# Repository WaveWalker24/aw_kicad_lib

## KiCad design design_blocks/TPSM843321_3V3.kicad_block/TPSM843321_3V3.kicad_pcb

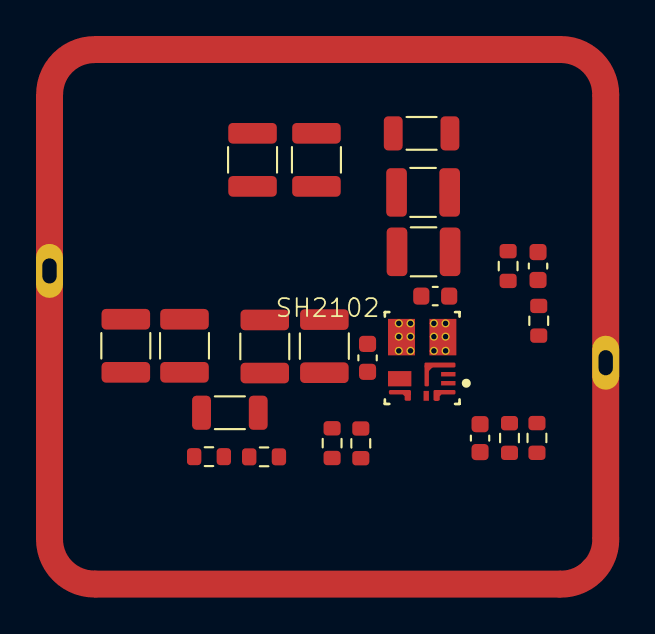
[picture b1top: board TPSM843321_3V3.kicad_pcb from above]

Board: 6 copper layers, 25 parts (0 on the bottom side), 10 nets, no tracks yet.

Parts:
C2017, C2018, C2019, C2020, C2038, C2039, C2040, C2041: 22uF; C_1210_3225Metric
C2021: 33nF; C_0603_1608Metric
C2022, C2024: 100nF; C_0603_1608Metric
C2023: 22pF; C_0603_1608Metric
FB2003, FB2004: 220Ohm @ 100MHz; L_1206_3216Metric
R2026, R2028, R2029: 0R; R_0603_1608Metric
R2030: 46.4k; R_0603_1608Metric
R2034: 10k; R_0603_1608Metric
R2035, R2036, R2037: 100k; R_0603_1608Metric
SH2102: RFShield_TwoPieces_Frame_W31.2mm_L30mm_H5mm; MS312-10
SH2103: RFShield_TwoPieces_Cover_W31.2mm_L30mm_H5mm; MS312-10C
U2003: TPSM843321RCJR; RCJ0009A-MFG

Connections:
/VDD_12V: C2017.1, C2018.1, FB2003.1, R2035.1
/fpga/PG: C2021.1, R2037.2, U2003.8 (SS_PG)
/fpga/TPS_VIN: C2019.1, C2020.1, C2022.1, FB2003.2, R2037.1, U2003.6 (VIN)
/fpga/TPS_VOUT: C2023.1, C2024.1, C2038.1, C2039.1, FB2004.1, R2030.1, U2003.4 (VOUT)
/fpga/VDD_3V3: C2040.1, C2041.1, FB2004.2
GND: C2017.2, C2018.2, C2019.2, C2020.2, C2021.2, C2022.2, C2024.2, C2038.2, C2039.2, C2040.2, C2041.2, R2028.2, R2029.2, R2034.2, R2036.2, SH2102.1 (Shield_1), U2003.3 (GND)
unnamed: R2026.2, R2035.2, R2036.1, U2003.1 (EN)
unnamed: C2023.2, R2030.2, R2034.1, U2003.2 (FB)
unnamed: R2029.1, U2003.7 (MODE)
unnamed: R2028.1, U2003.9 (RT_SYNC)

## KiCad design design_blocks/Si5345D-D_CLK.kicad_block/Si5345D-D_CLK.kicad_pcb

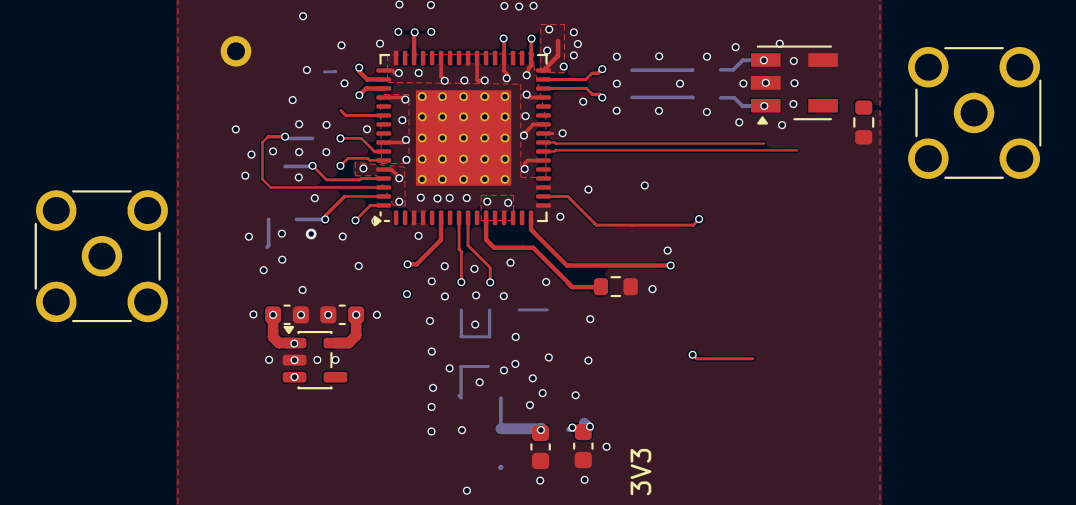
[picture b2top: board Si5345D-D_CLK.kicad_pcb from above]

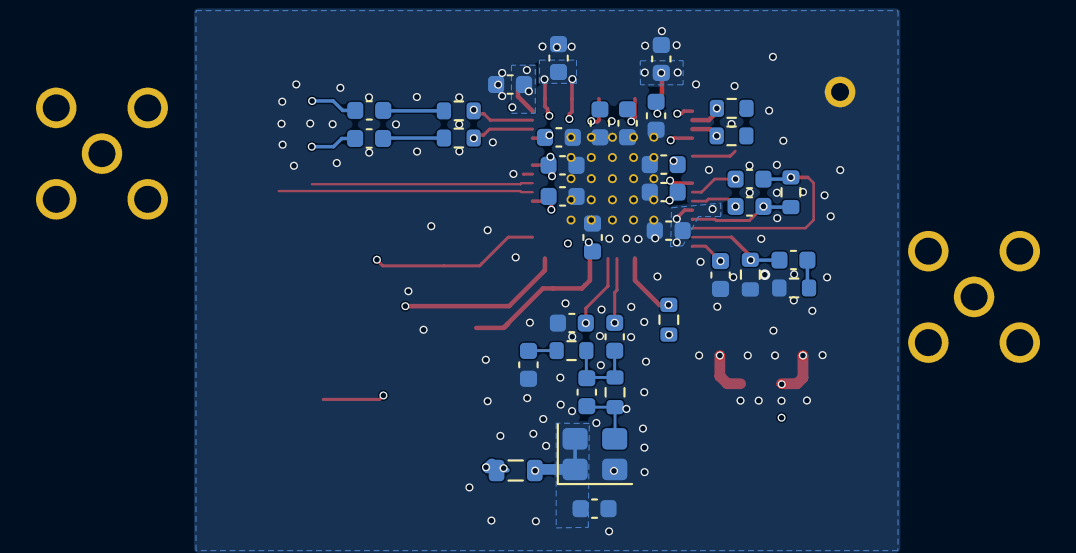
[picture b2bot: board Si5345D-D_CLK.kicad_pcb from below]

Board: 8 copper layers, 48 parts (36 on the bottom side), 28 nets.

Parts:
C6: 12pF; C_0603_1608Metric
C7, C8, C9, C15, C16, C17, C27, C30, C31, C1053: 100nF; C_0603_1608Metric
C10, C11, C1009, C1024, C1042, C1043, C1044, C1045, C1046, C1047, C1048, C1049, C1050, C1051, C1052, C1072, C1073: 1uF; C_0603_1608Metric
D2001, D2002: ESD_3.3V; R_0603_1608Metric
FB1003: 600 Ohm @ 100 MHz; L_0805_2012Metric
J1, J2: Conn_Coaxial_Small; SMA_Molex_73251-2200_Horizontal
J4011: TP; Testpoint_2.54mm
R24: 453R; R_0603_1608Metric
R25: 549R; R_0603_1608Metric
R30: 10k; R_0603_1608Metric
R31: 100R; R_0603_1608Metric
R37: 49.9R; R_0603_1608Metric
R1033, R1034, R4001, R4010: 28; R_0603_1608Metric
R1057: 4.75k; R_0603_1608Metric
TR4001: TC2-1TX+; Mini-Circuits_AT1521
U4: Si5345D-D; QFN-64-1EP_9x9mm_P0.5mm_EP5.3x5.3mm_ThermalVias
U1023: ADP150AUJZ-1.8-R7; TSOT-23-5
Y1: 7X48070007

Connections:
/3V3: C1042.1, C1043.1, C1044.1, C1045.1, C1046.1, C1047.1, C1048.1, C1049.1, C1051.1, C1052.1, C1072.1, R1057.1, U4.13 (VDDA), U4.22 (VDDO0), U4.26 (VDDO1), U4.29 (VDDO2), U4.33 (VDDO3), U4.36 (VDDO4), U4.39 (I2C_SEL), U4.40 (VDDO5), U4.43 (VDDO6), U4.49 (VDDO7), U4.52 (VDDO8), U4.57 (VDDO9), U1023.1 (VIN), U1023.3 (EN)
/clk/1V8: C1009.1, C1024.1, C1050.1, C1073.1, J4011.1 (Pin_1_1), U4.32 (VDD), U4.46 (VDD), U4.60 (VDD), U1023.5 (VOUT)
/clk/3.3V: C10.1, FB1003.1
/clk/3V3_XO: C11.1, C1053.1, FB1003.2, Y1.1 (EN), Y1.4 (Vdd)
/clk/CLK_OUT_N: C27.1, R1033.2
/clk/CLK_OUT_P: C17.1, R1034.2
/clk/Clock Out: D2002.1 (A1), J2.1 (In), TR4001.6 (Primary_Dot)
/clk/RESET: R1057.2, U4.6 (~RST)
/clk/XA: C8.1, U4.8 (XA)
/clk/XB: C9.2, U4.9 (XB)
/clk/Zero_Delay_N: C16.2, U4.58 (OUT9b)
/clk/Zero_Delay_P: C15.2, U4.59 (OUT9)
GND: C7.1, C9.1, C10.2, C11.2, C31.1, C1009.2, C1024.2, C1042.2, C1043.2, C1044.2, C1045.2, C1046.2, C1047.2, C1048.2, C1049.2, C1050.2, C1051.2, C1052.2, C1053.2, C1072.2, C1073.2, D2001.2 (A2), D2002.2 (A2), J1.2 (Ext), J2.2 (Ext), R30.2, R37.2, TR4001.2 (SECONDARY_CT), TR4001.4 (PRIMARY), U4.3 (IN_SEL0), U4.4 (IN_SEL1), U4.17 (A1/SDO), U4.19 (A0/~CS), U4.25 (FDEC), U4.48 (FINC), U4.65 (GND), U1023.2 (GND), Y1.2 (GND)
unnamed: C6.2, C8.2, R24.2, R25.1
unnamed: C7.2, R25.2
unnamed: C30.2, D2001.1 (A1), U4.63 (IN0)
unnamed: C30.1, J1.1 (In), R37.1
unnamed: C17.2, TR4001.3 (SECONDARY)
unnamed: C27.2, TR4001.1 (SECONDARY_DOT)
unnamed: C31.2, U4.64 (IN0b)
unnamed: C16.1, R31.2, U4.62 (IN3b/FB_INb)
unnamed: C15.1, R31.1, U4.61 (IN3/FB_IN)
unnamed: R1034.1, U4.31 (OUT2)
unnamed: R1033.1, U4.30 (OUT2b)
unnamed: R4010.1, U4.51 (OUT7)
unnamed: R4001.1, U4.50 (OUT7b)
unnamed: R30.1, U4.11 (~OE)
unnamed: C6.1, R24.1, Y1.3 (OUT)
